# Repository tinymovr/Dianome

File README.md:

# Dianome
Schematic and Board file for the Dianome R2 PDB

[OSHW] GR000006 | Certified open source hardware | oshwa.org/cert

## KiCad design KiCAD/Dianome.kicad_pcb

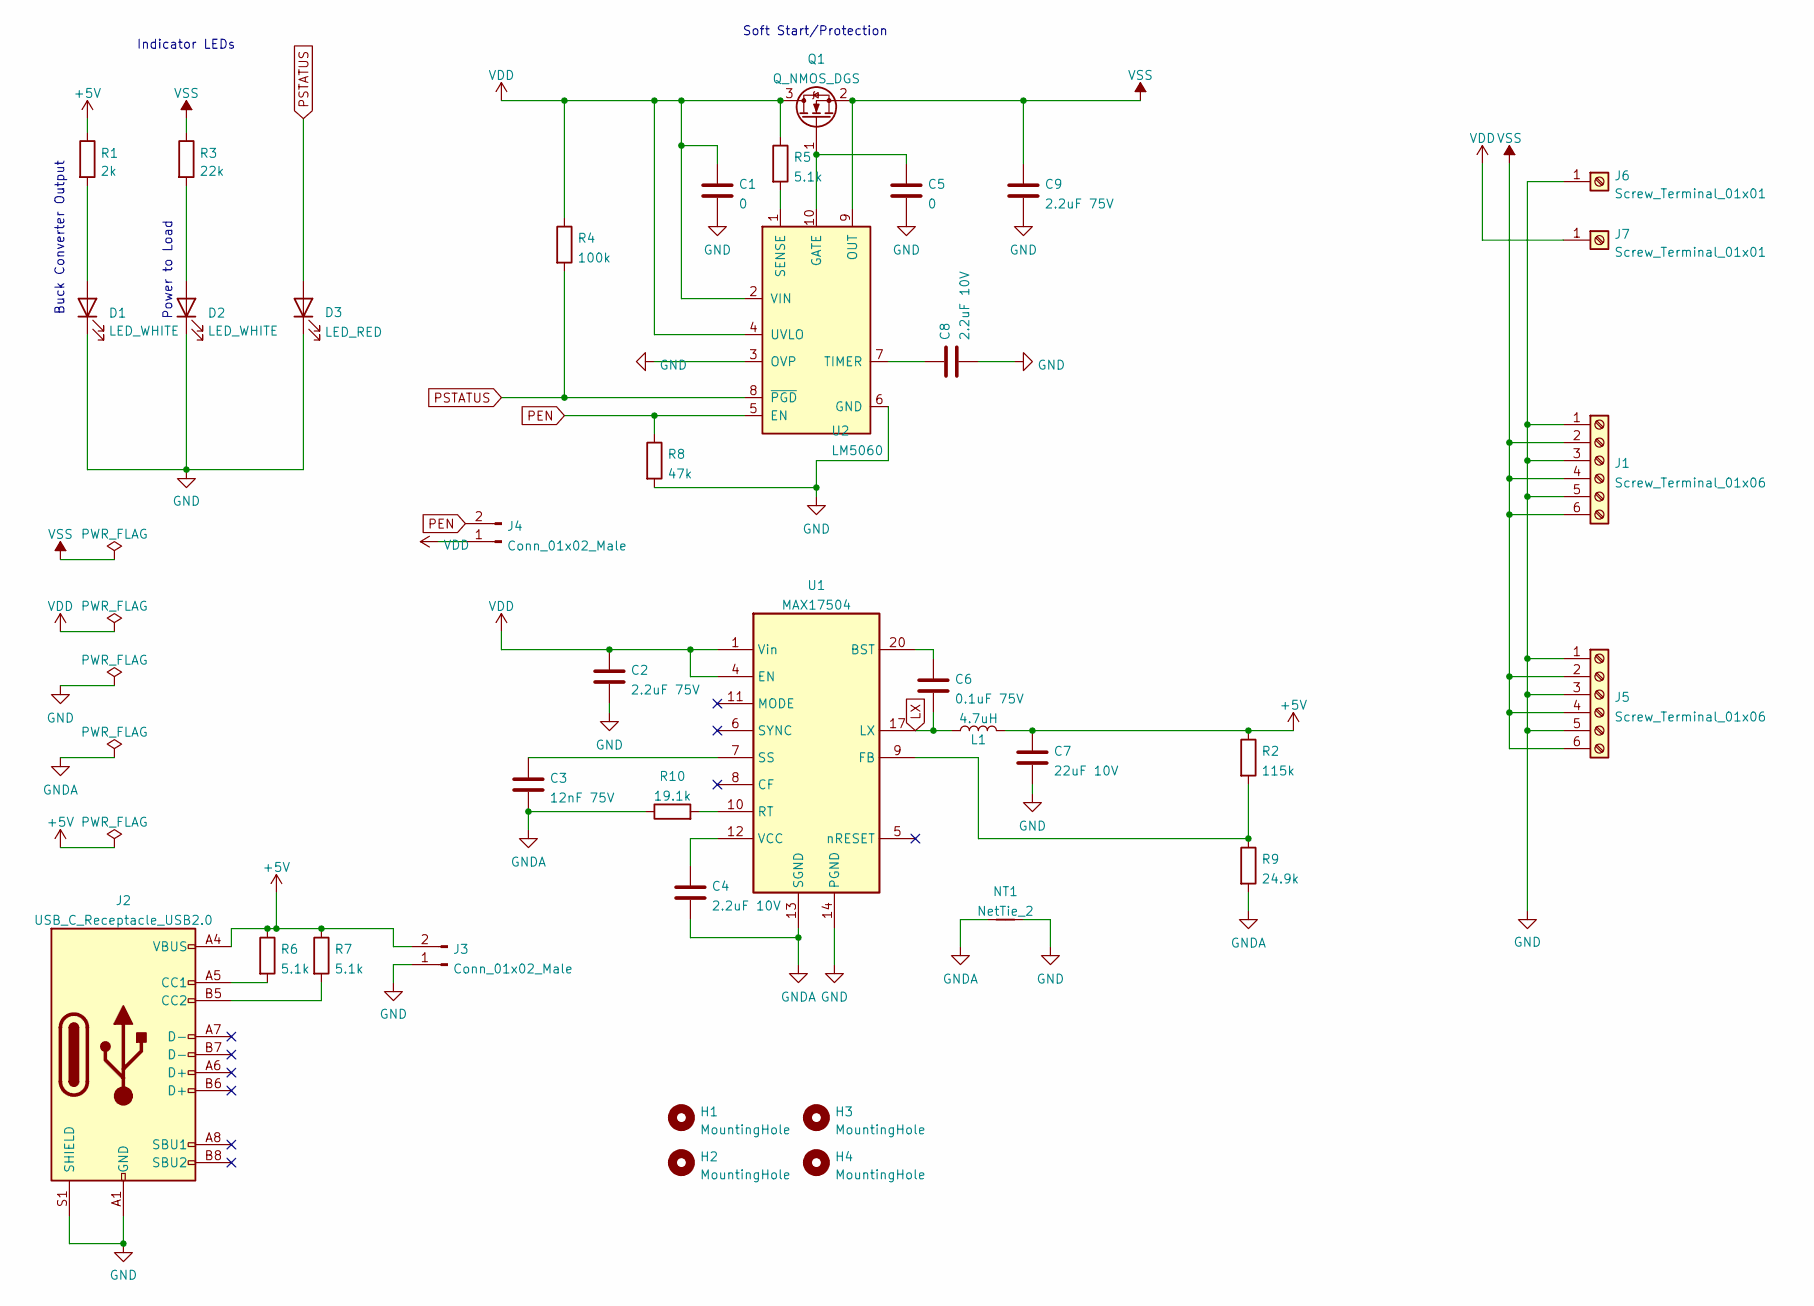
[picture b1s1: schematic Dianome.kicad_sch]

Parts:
C1: 0
C2, C9: 2.2uF 75V; C_1210_3225Metric
C3: 12nF 75V; C_0603_1608Metric
C4, C8: 2.2uF 10V; C_0603_1608Metric
C5: 0; C_0603_1608Metric
C6: 0.1uF 75V; C_0603_1608Metric
C7: 22uF 10V; C_1210_3225Metric
D1, D2: LED_WHITE; LED_0603_1608Metric
D3: LED_RED; LED_0603_1608Metric
H1, H2, H3, H4: MountingHole; MountingHole_3.2mm_M3_DIN965_Pad
J1, J5: Screw_Terminal_01x06; TerminalBlock_bornier-6_P5.08mm
J2: USB_C_Receptacle_USB2.0; USB_C_Receptacle_HRO_TYPE-C-31-M-12
J3, J4: Conn_01x02_Male; PinHeader_1x02_P2.54mm_Vertical
J6, J7: Screw_Terminal_01x01; MountingHole_4.3mm_M4_DIN965_Pad_TopBottom
L1: 4.7uH; L_Coilcraft_XAL60xx_6.36x6.56mm
NT1: NetTie_2; NetTie-2_SMD_Pad0.5mm
Q1: Q_NMOS_DGS; PQFN_8x8
R1: 2k; R_0603_1608Metric
R2: 115k; R_0603_1608Metric
R3: 22k; R_0603_1608Metric
R4: 100k; R_0603_1608Metric
R5, R6, R7: 5.1k; R_0603_1608Metric
R8: 47k; R_0603_1608Metric
R9: 24.9k; R_0603_1608Metric
R10: 19.1k; R_0603_1608Metric
U1: ΜΑΧ17504; MAX17504
U2: LM5060; MSOP-10_3x3mm_P0.5mm

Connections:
+5V: C7.1, J2.A4 (VBUS), J2.A9 (VBUS), J2.B4 (VBUS), J2.B9 (VBUS), J3.2, L1.2, R1.1, R2.1, R6.1, R7.1
GND: C1.2, C2.2, C5.2, C7.2, C8.2, C9.2, D1.1 (K), D2.1 (K), D3.1 (K), J1.1, J1.3, J1.5, J2.A1 (GND), J2.A12 (GND), J2.B1 (GND), J2.B12 (GND), J2.S1 (SHIELD), J3.1, J5.1, J5.3, J5.5, J6.1, NT1.2, R8.2, U1.14 (PGND), U2.3 (OVP), U2.6 (GND)
GNDA: C3.2, C4.2, NT1.1, R9.2, R10.1, U1.13 (SGND)
LX: C6.2, L1.1, U1.17 (LX)
unnamed: C3.1, U1.7 (SS)
unnamed: C4.1, U1.12 (VCC)
unnamed: C5.1, Q1.1 (G), U2.10 (GATE)
unnamed: C6.1, U1.20 (BST)
unnamed: C8.1, U2.7 (TIMER)
unnamed: D1.2 (A), R1.2
unnamed: D2.2 (A), R3.2
unnamed: J2.A5 (CC1), R6.2
unnamed: J2.B5 (CC2), R7.2
unnamed: R2.2, R9.1, U1.9 (FB)
unnamed: R5.2, U2.1 (SENSE)
unnamed: R10.2, U1.10 (RT)
PEN: J4.2, R8.1, U2.5 (EN)
PSTATUS: D3.2 (A), R4.2, U2.8 (~PGD)
VDD: C1.1, C2.1, J4.1, J7.1, Q1.3 (D), R4.1, R5.1, U1.1 (Vin), U1.4 (EN), U2.2 (VIN), U2.4 (UVLO)
VSS: C9.1, J1.2, J1.4, J1.6, J5.2, J5.4, J5.6, Q1.2 (S), R3.1, U2.9 (OUT)

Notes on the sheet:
Buck Converter Output
Indicator LEDs
Power to Load
Soft Start/Protection

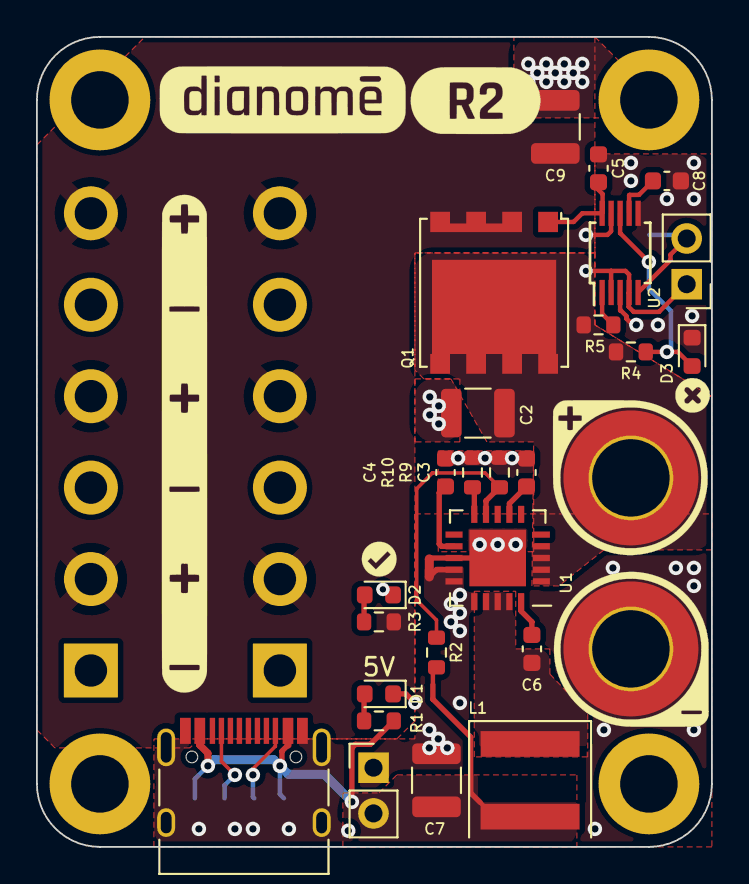
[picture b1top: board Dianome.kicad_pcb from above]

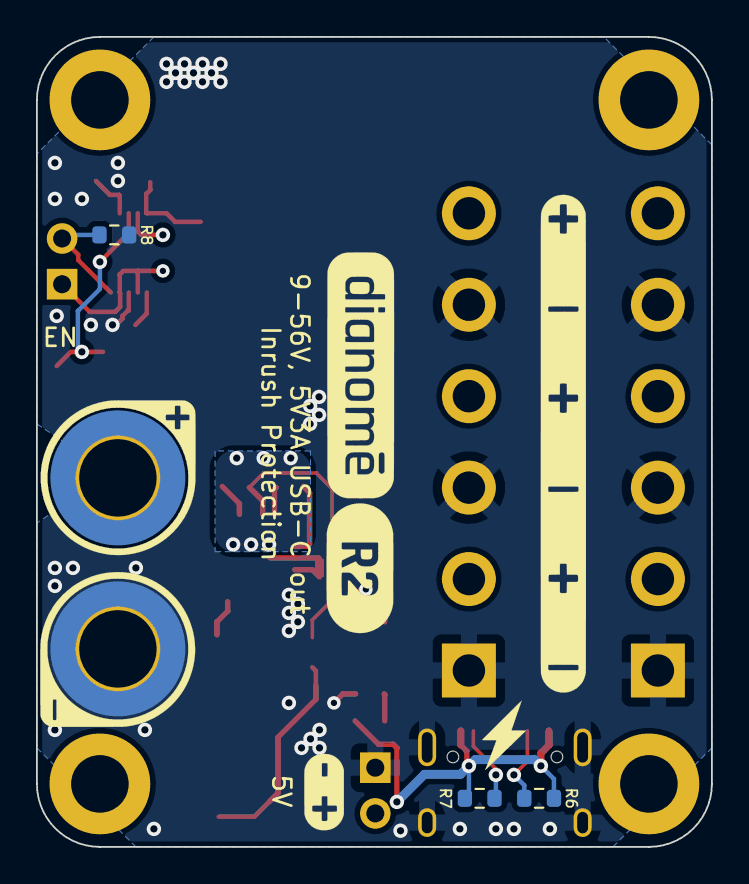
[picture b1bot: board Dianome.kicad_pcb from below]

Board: 2 copper layers, 37.5 x 45.0 mm, 49 parts (9 on the bottom side), 20 nets.

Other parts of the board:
Ref**: Val**; logo
Ref**#2, Ref**#8: Val**; plus
Ref**#3, Ref**#10: Val**; pol_multi
Ref**#4: Val**; fault
Ref**#5: Val**; ok
Ref**#6, Ref**#9: Val**; minus
Ref**#7: Val**; plus_minus
Ref**#11: Val**; lightning
Ref**#12: Val**; logo

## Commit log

2021-08-30 Add board and schematic
2021-09-01 Rename PowerDistv4.brd to Dianome.brd
2021-09-01 Rename PowerDistv4.sch to Dianome.sch
2021-09-11 add docs
2021-09-11 update gitignore
2022-12-20 update project files
2022-12-20 minor layout changes
2022-12-20 add PDF
2022-12-20 Update LICENSE
2022-12-20 Create LICENSE
2022-12-20 Create COPYRIGHT
2022-12-22 Add OSHW certification info
2024-02-22 Add STEP file
